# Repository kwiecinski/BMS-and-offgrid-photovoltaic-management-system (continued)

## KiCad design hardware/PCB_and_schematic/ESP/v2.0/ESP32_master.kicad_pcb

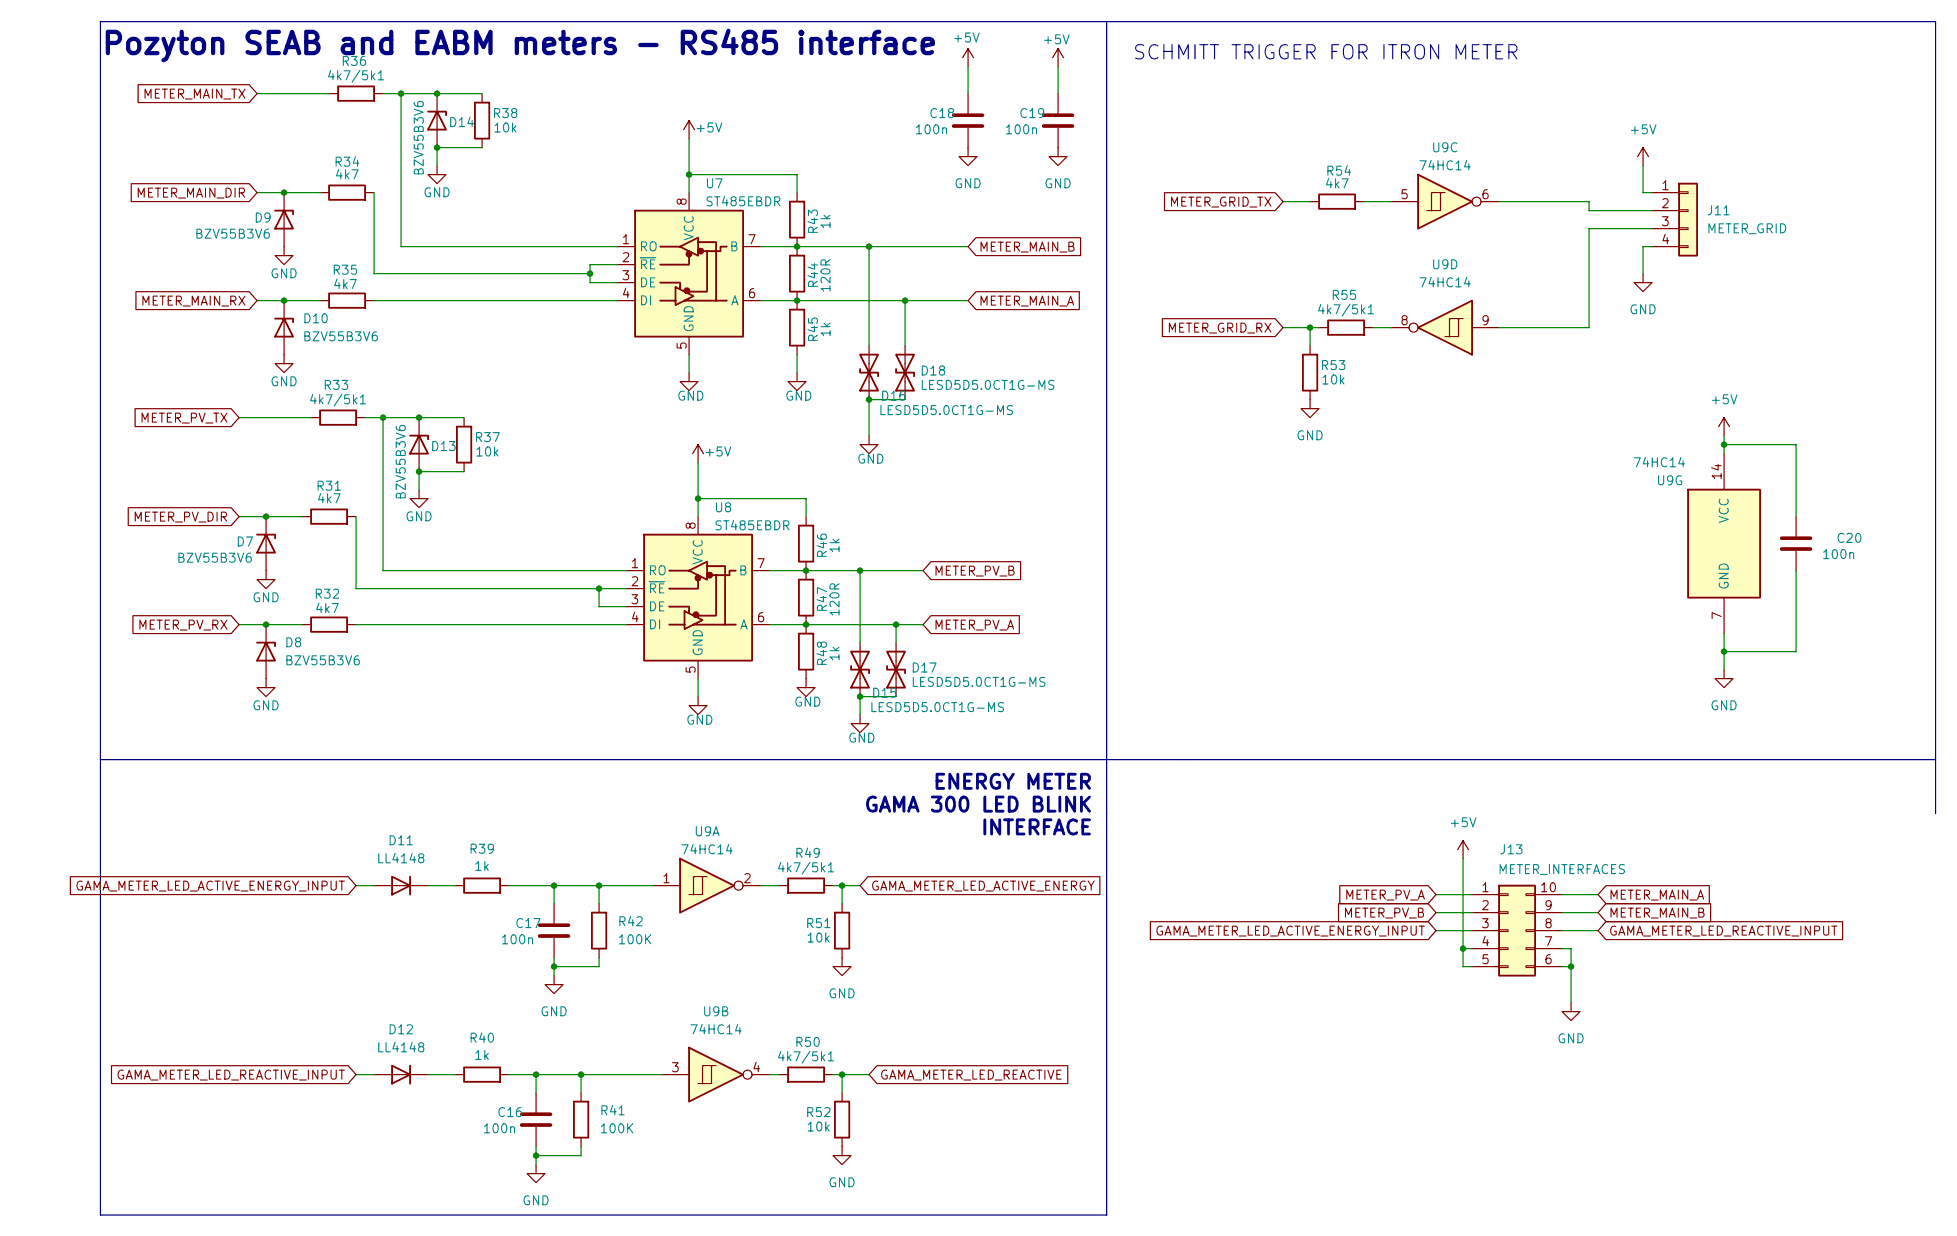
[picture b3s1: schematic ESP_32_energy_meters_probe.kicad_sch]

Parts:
C16, C17, C18, C19, C20: 100n; C_0805_2012Metric_Pad1.18x1.45mm_HandSolder
D7, D8, D9, D10, D13, D14: BZV55B3V6; D_MiniMELF
D11, D12: LL4148; D_MiniMELF
D15, D16, D17, D18: LESD5D5.0CT1G-MS; D_SOD-523
J11: METER_GRID; JST_XA_B04B-XASK-1_1x04_P2.50mm_Vertical
J13: METER_INTERFACES; CDDC-1,5-5-PV-3,5
R31, R32, R34, R35, R54: 4k7; R_0805_2012Metric_Pad1.20x1.40mm_HandSolder
R33, R36, R49, R50, R55: 4k7/5k1; R_0805_2012Metric_Pad1.20x1.40mm_HandSolder
R37, R38, R51, R52, R53: 10k; R_0805_2012Metric_Pad1.20x1.40mm_HandSolder
R39, R40, R43, R45, R46, R48: 1k; R_0805_2012Metric_Pad1.20x1.40mm_HandSolder
R41, R42: 100K; R_0805_2012Metric_Pad1.20x1.40mm_HandSolder
R44, R47: 120R; R_0805_2012Metric_Pad1.20x1.40mm_HandSolder
U7, U8: ST485EBDR; SOIC-8_3.9x4.9mm_P1.27mm
U9: 74HC14; SOIC-14_3.9x8.7mm_P1.27mm

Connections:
+5V: C18.1, C19.1, C20.1, J11.1, J13.4, J13.5, R43.2, R46.2, U7.8 (VCC), U8.8 (VCC), U9.14 (VCC); also elsewhere on the board
GAMA_METER_LED_ACTIVE_ENERGY: R49.1, R51.2; also elsewhere on the board
GAMA_METER_LED_ACTIVE_ENERGY_INPUT: D11.2 (A), J13.3
GAMA_METER_LED_REACTIVE: R50.1, R52.2; also elsewhere on the board
GAMA_METER_LED_REACTIVE_INPUT: D12.2 (A), J13.8
GND: C16.2, C17.2, C18.2, C19.2, C20.2, D7.2 (A), D8.2 (A), D9.2 (A), D10.2 (A), D13.2 (A), D14.2 (A), D15.1 (A1), D16.1 (A1), D17.1 (A1), D18.1 (A1), J11.4, J13.6, J13.7, R37.1, R38.1, R41.1, R42.1, R45.1, R48.1, R51.1, R52.1, R53.1, U7.5 (GND), U8.5 (GND), U9.7 (GND); also elsewhere on the board
METER_GRID_RX: R53.2, R55.1; also elsewhere on the board
METER_GRID_TX: R54.1; also elsewhere on the board
METER_MAIN_A: D18.2 (A2), J13.10, R44.1, R45.2, U7.6 (A)
METER_MAIN_B: D16.2 (A2), J13.9, R43.1, R44.2, U7.7 (B)
METER_MAIN_DIR: D9.1 (K), R34.1; also elsewhere on the board
METER_MAIN_RX: D10.1 (K), R35.1; also elsewhere on the board
METER_MAIN_TX: R36.1; also elsewhere on the board
METER_PV_A: D17.2 (A2), J13.1, R47.1, R48.2, U8.6 (A)
METER_PV_B: D15.2 (A2), J13.2, R46.1, R47.2, U8.7 (B)
METER_PV_DIR: D7.1 (K), R31.1; also elsewhere on the board
METER_PV_RX: D8.1 (K), R32.1; also elsewhere on the board
METER_PV_TX: R33.1; also elsewhere on the board
unnamed: C16.1, R40.2, R41.2, U9.3
unnamed: C17.1, R39.2, R42.2, U9.1
unnamed: D11.1 (K), R39.1
unnamed: D12.1 (K), R40.1
unnamed: D13.1 (K), R33.2, R37.2, U8.1 (RO)
unnamed: D14.1 (K), R36.2, R38.2, U7.1 (RO)
unnamed: J11.2, U9.6
unnamed: J11.3, U9.9
unnamed: R49.2, U9.2
unnamed: R50.2, U9.4
unnamed: R54.2, U9.5
unnamed: R55.2, U9.8
unnamed: R34.2, U7.2 (~RE), U7.3 (DE)
unnamed: R35.2, U7.4 (DI)
unnamed: R31.2, U8.2 (~RE), U8.3 (DE)
unnamed: R32.2, U8.4 (DI)

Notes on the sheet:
Pozyton SEAB and EABM meters - RS485 interface
ENERGY METER GAMA 300 LED BLINK INTERFACE
SCHMITT TRIGGER FOR ITRON METER

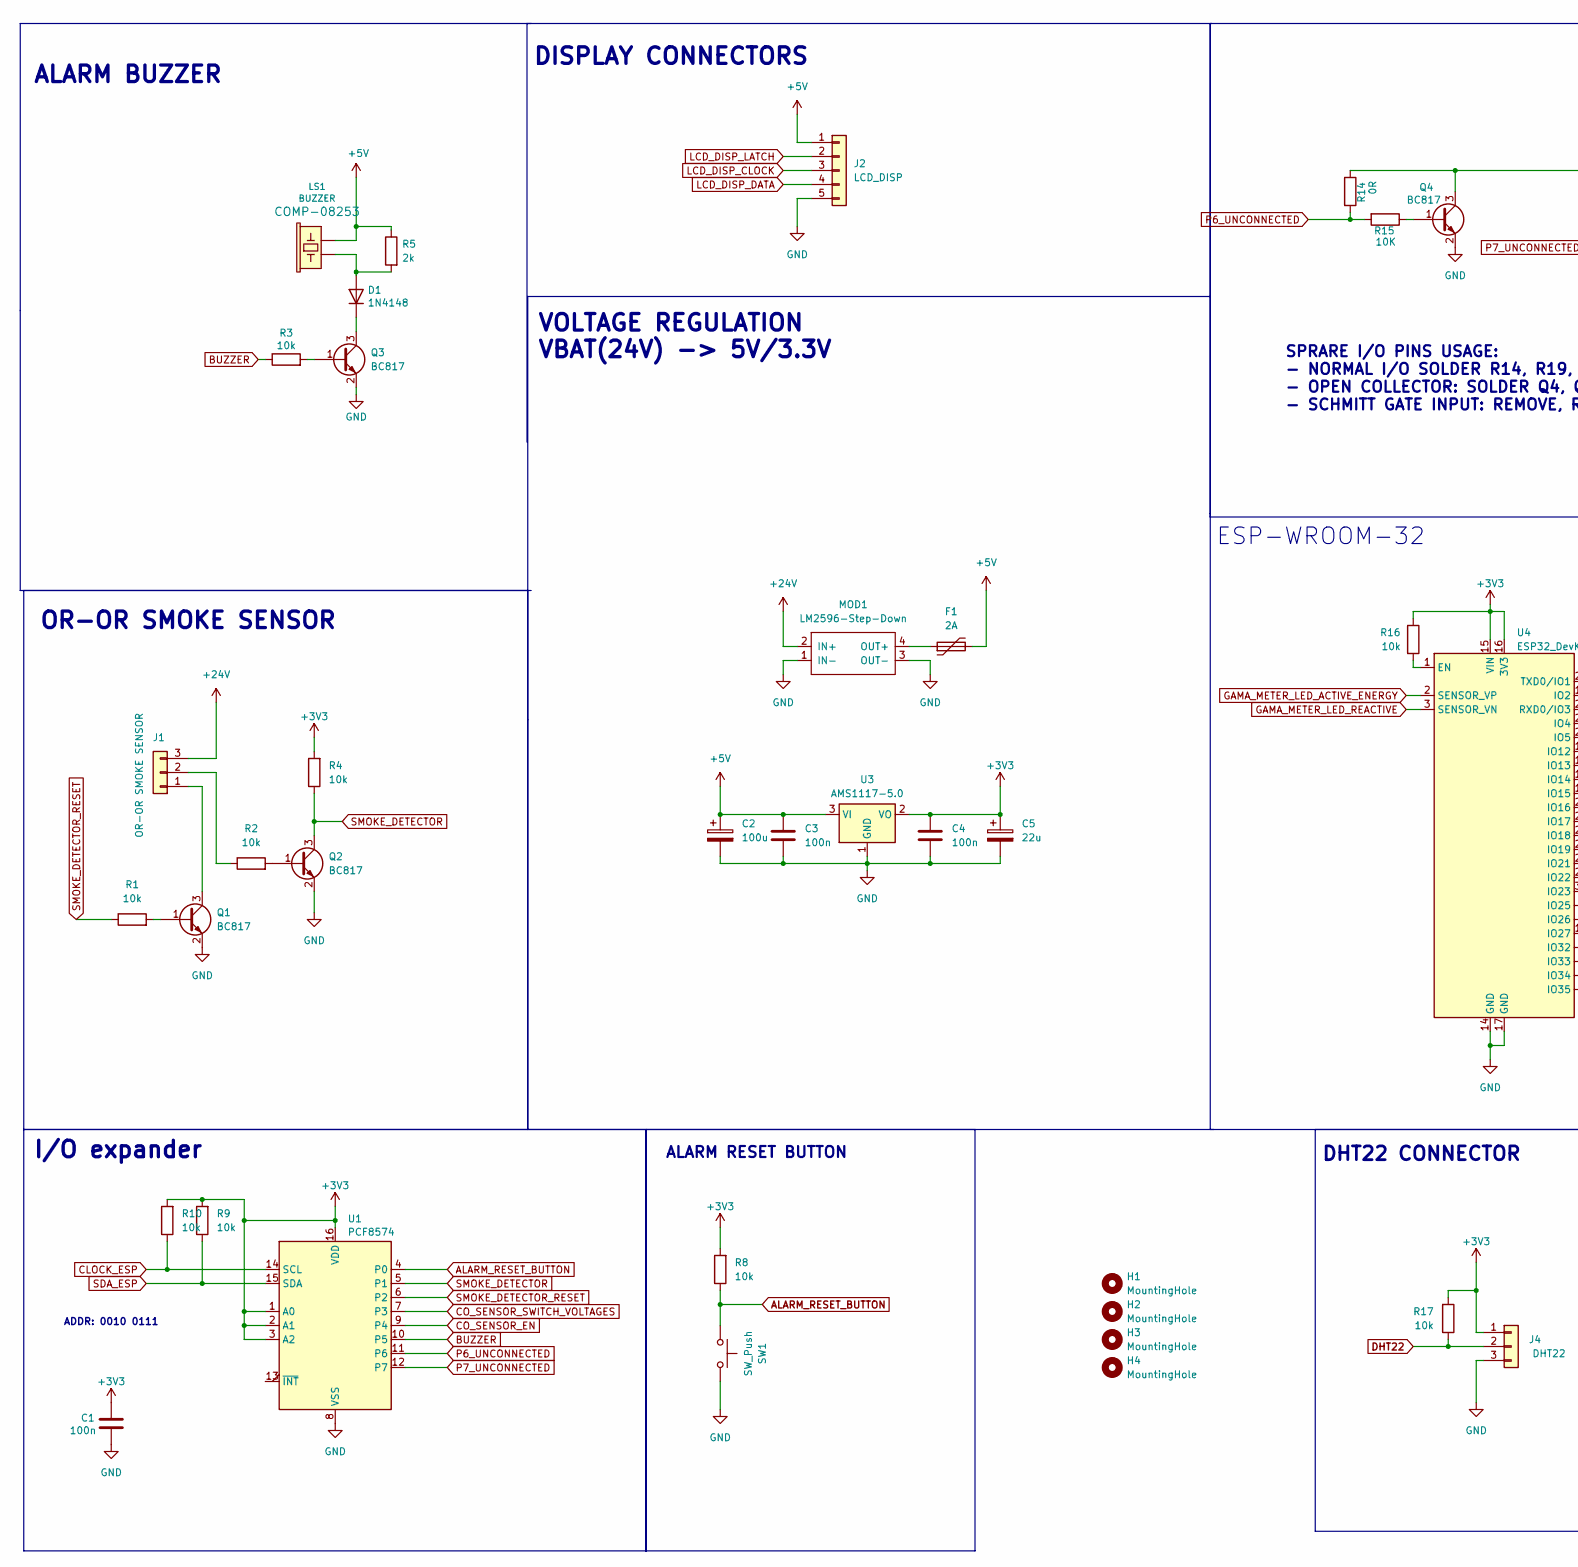
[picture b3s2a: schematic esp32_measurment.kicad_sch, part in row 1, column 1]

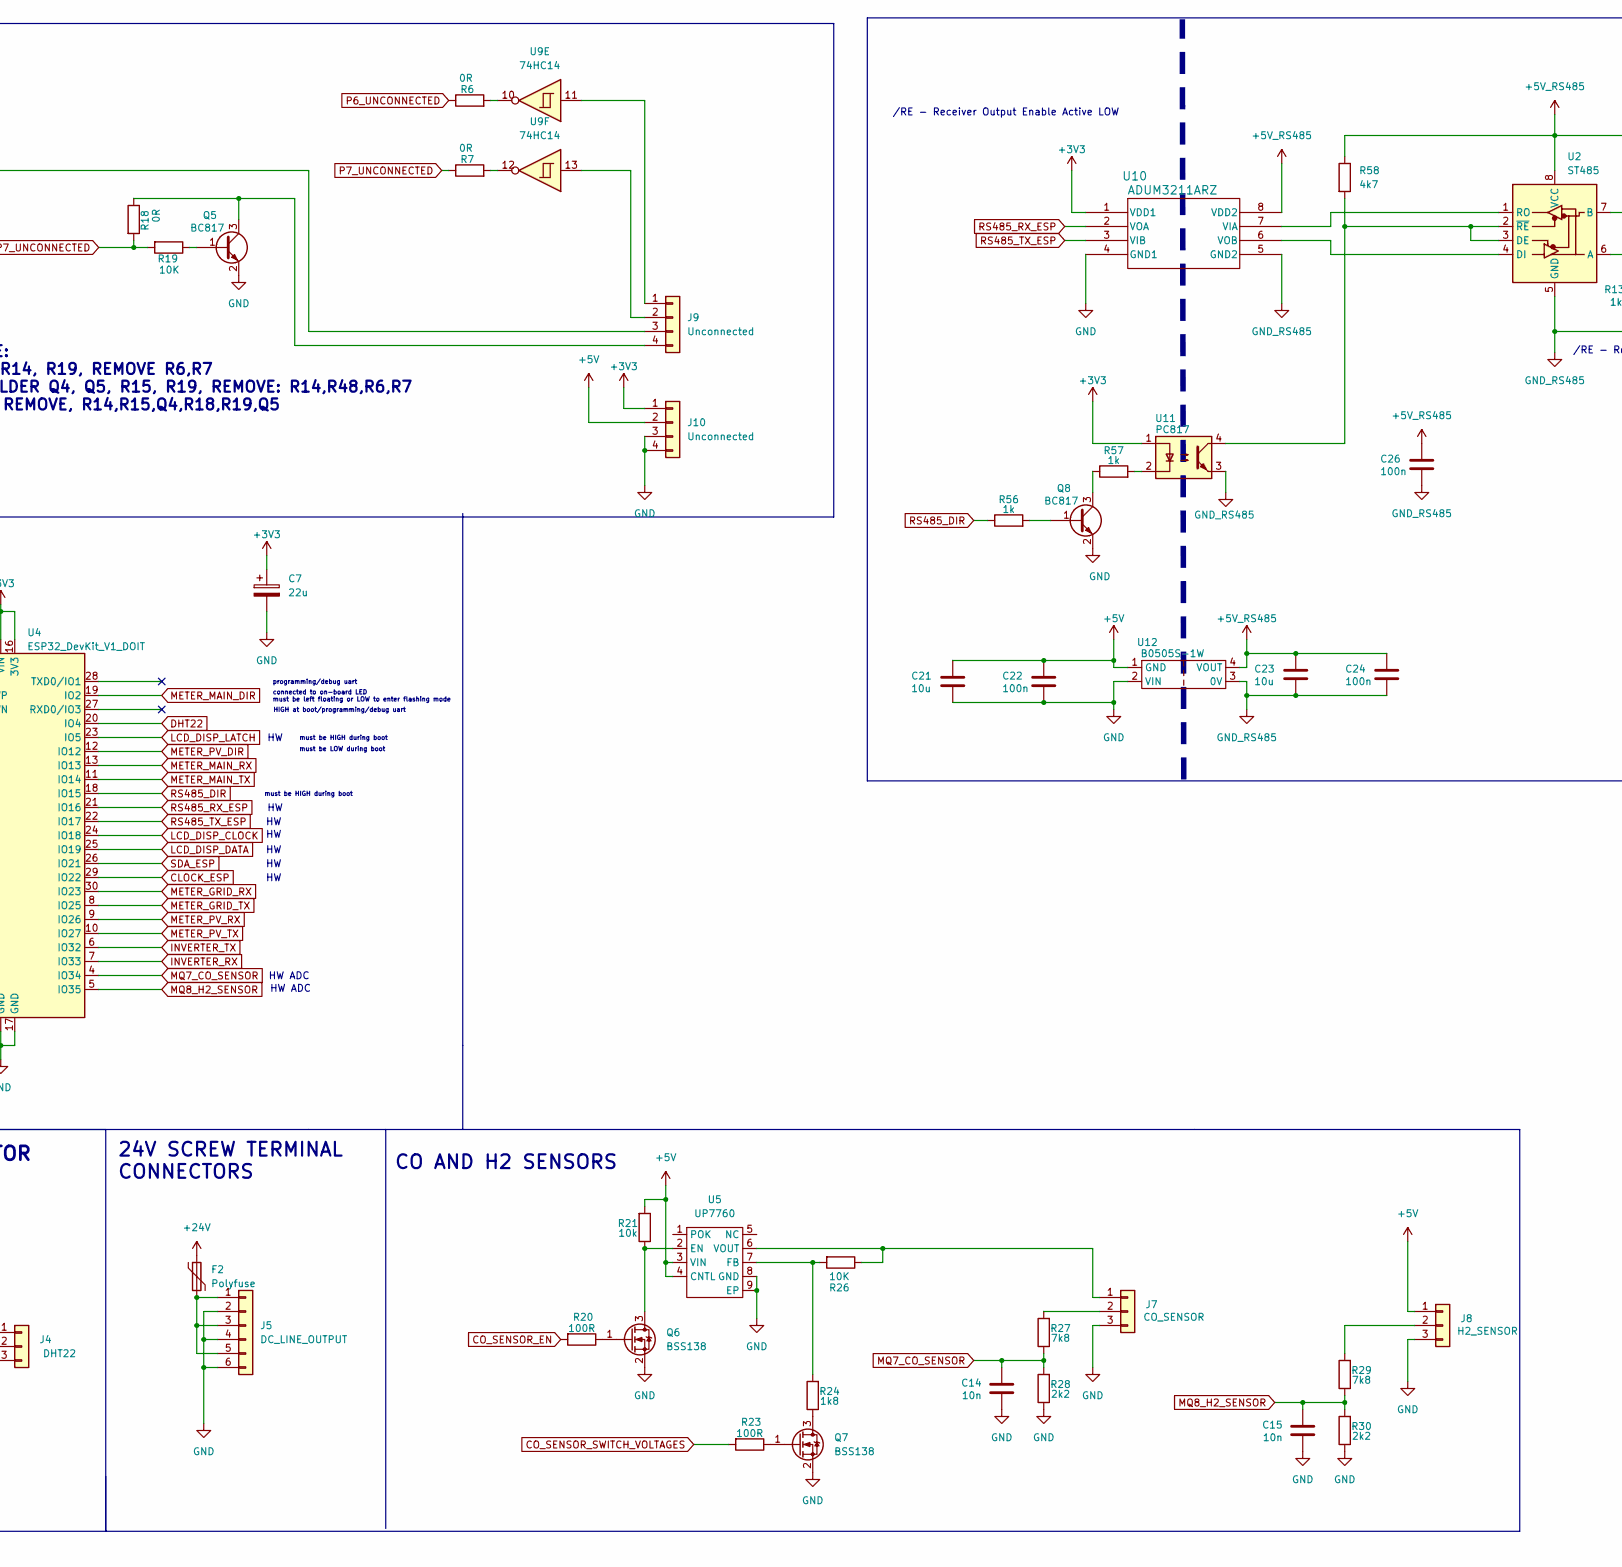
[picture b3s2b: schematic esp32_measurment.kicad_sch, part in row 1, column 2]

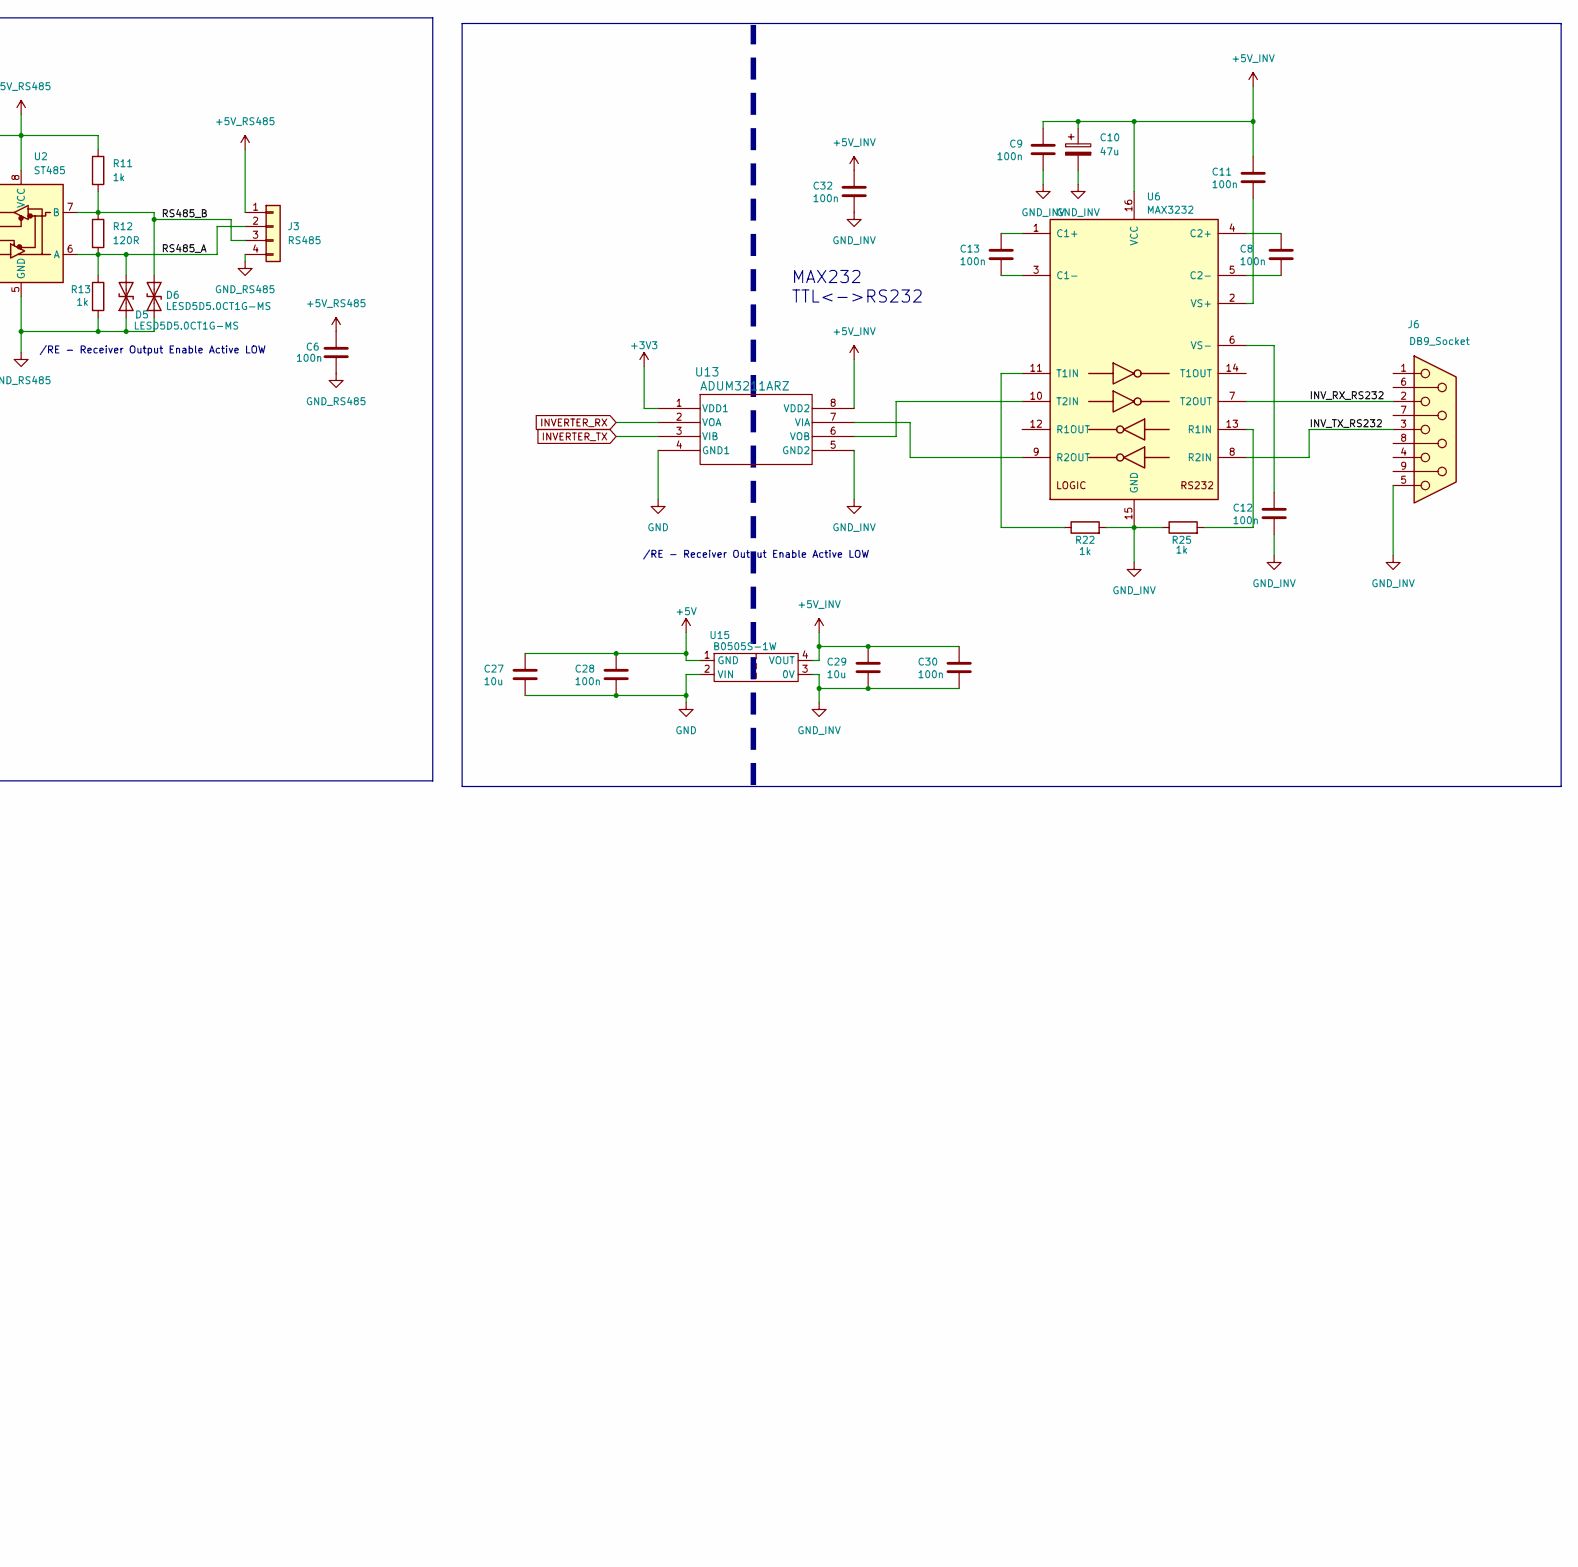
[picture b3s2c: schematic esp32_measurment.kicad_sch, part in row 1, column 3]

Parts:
C1, C3, C4, C6, C8, C11, C12, C13, C22, C24, C26, C28, C30, C32: 100n; C_0805_2012Metric_Pad1.18x1.45mm_HandSolder
C2: 100u; CP_Radial_D4.0mm_P1.50mm
C5: 22u; CP_Radial_D4.0mm_P1.50mm
C7: 22u; CP_Radial_D5.0mm_P2.00mm
C9: 100n; C_0805_2012Metric
C10: 47u; CP_Radial_D5.0mm_P2.00mm
C14, C15: 10n; C_0805_2012Metric
C21, C23, C27, C29: 10u; C_1206_3216Metric
D1: 1N4148; D_MiniMELF
D5, D6: LESD5D5.0CT1G-MS; D_SOD-523
F1: 2A; Fuse_2512_6332Metric_Pad1.52x3.35mm_HandSolder
F2: Polyfuse; Fuse_2920_7451Metric
H1, H2, H3, H4: MountingHole; Mount-Hole-3mm
J1: OR-OR SMOKE SENSOR; JST_XA_B03B-XASK-1_1x03_P2.50mm_Vertical
J2: LCD_DISP; JST_XA_B05B-XASK-1_1x05_P2.50mm_Vertical
J3: RS485; JST_XH_B4B-XH-A_1x04_P2.50mm_Vertical
J4: DHT22; JST_XA_1x03_P2.54mm_Vertical
J5: DC_LINE_OUTPUT; Screw-Terminal-P6-rast-5mm-6,7x30
J6: DB9_Socket; DSUB-9_Female_Horizontal_P2.77x2.84mm_EdgePinOffset7.70mm_H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
J7: CO_SENSOR; JST_XA_B03B-XASK-1_1x03_P2.50mm_Vertical
J8: H2_SENSOR; JST_XA_B03B-XASK-1_1x03_P2.50mm_Vertical
J9, J10: Unconnected; JST_XA_B04B-XASK-1_1x04_P2.50mm_Vertical
LS1: BUZZER; Buzzer
MOD1: LM2596-Step-Down; LM2596-Step-Down-Conv
Q1, Q2, Q3, Q4, Q5, Q8: BC817; SOT-23
Q6, Q7: BSS138; SOT-23
R1, R2, R3, R4, R8, R9, R10, R16, R17, R21: 10k; R_0805_2012Metric_Pad1.20x1.40mm_HandSolder
R5: 2k; C_0805_2012Metric
R6, R7, R14, R18: 0R; R_0805_2012Metric_Pad1.20x1.40mm_HandSolder
R11, R13, R22, R25, R56, R57: 1k; R_0805_2012Metric_Pad1.20x1.40mm_HandSolder
R12: 120R; R_0805_2012Metric_Pad1.20x1.40mm_HandSolder
R15, R19, R26: 10K; R_0805_2012Metric_Pad1.20x1.40mm_HandSolder
R20, R23: 100R; R_0805_2012Metric_Pad1.20x1.40mm_HandSolder
R24: 1k8; R_0805_2012Metric_Pad1.20x1.40mm_HandSolder
R27, R29: 7k8; R_0805_2012Metric_Pad1.20x1.40mm_HandSolder
R28, R30: 2k2; R_0805_2012Metric_Pad1.20x1.40mm_HandSolder
R58: 4k7; R_0805_2012Metric_Pad1.20x1.40mm_HandSolder
SW1: SW_Push; JST_XA_B02B-XASK-1_1x02_P2.50mm_Vertical
U1: PCF8574; DIP-16_W7.62mm_LongPads
U2: ST485; SOIC-8_3.9x4.9mm_P1.27mm
U3: AMS1117-5.0; SOT-223-3_TabPin2
U4: ESP32_DevKit_V1_DOIT; esp32_devkit_v1_doit
U5: UP7760; SOIC-8-1EP_3.9x4.9mm_P1.27mm_EP2.41x3.81mm
U6: MAX3232; SO-16_3.9x9.9mm_P1.27mm
U9: 74HC14; SOIC-14_3.9x8.7mm_P1.27mm
U10, U13: ADUM3211ARZ; SO-8_3.9x4.9mm_P1.27mm
U11: PC817; DIP-4_W7.62mm
U12, U15: B0505S-1W; B0505S

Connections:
+3V3: C1.1, C4.1, C5.1, C7.1, J4.1, J10.1, R4.2, R8.2, R9.2, R10.2, R16.1, R17.2, U1.1 (A0), U1.2 (A1), U1.3 (A2), U1.16 (VDD), U3.2 (VO), U4.15 (VIN), U4.16 (3V3), U10.1 (VDD1), U11.1, U13.1 (VDD1)
+5V: C2.1, C3.1, C21.1, C22.1, C27.1, C28.1, F1.2, J2.1, J8.1, J10.2, LS1.- (2), R5.1, R21.2, U3.3 (VI), U5.3 (VIN), U5.4 (CNTL), U12.1 (GND), U15.1 (GND); also elsewhere on the board
+5V_INV: C9.2, C10.1, C11.1, C29.1, C30.1, C32.1, U6.16 (VCC), U13.8 (VDD2), U15.4 (VOUT)
+5V_RS485: C6.1, C23.1, C24.1, C26.1, J3.1, R11.1, R58.1, U2.8 (VCC), U10.8 (VDD2), U12.4 (VOUT)
+24V: F2.1, J1.3, MOD1.2 (IN+)
/ESP32_Measurment_Board/INV_RX_RS232: J6.2, U6.7 (T2OUT)
/ESP32_Measurment_Board/INV_TX_RS232: J6.3, U6.8 (R2IN)
/ESP32_Measurment_Board/RS485_A: D5.2 (A2), J3.2, R12.2, R13.1, U2.6 (A)
/ESP32_Measurment_Board/RS485_B: D6.2 (A2), J3.3, R11.2, R12.1, U2.7 (B)
ALARM_RESET_BUTTON: R8.1, SW1.1, U1.4 (P0)
BUZZER: R3.1, U1.10 (P5)
CLOCK_ESP: R10.1, U1.14 (SCL), U4.29 (IO22)
CO_SENSOR_EN: R20.2, U1.9 (P4)
CO_SENSOR_SWITCH_VOLTAGES: R23.2, U1.7 (P3)
DHT22: J4.2, R17.1, U4.20 (IO4)
GAMA_METER_LED_ACTIVE_ENERGY: U4.2 (SENSOR_VP); also elsewhere on the board
GAMA_METER_LED_REACTIVE: U4.3 (SENSOR_VN); also elsewhere on the board
GND: C1.2, C2.2, C3.2, C4.2, C5.2, C7.2, C14.1, C15.1, C21.2, C22.2, C27.2, C28.2, J2.5, J4.3, J5.2, J5.4, J5.6, J7.3, J8.3, J10.3, J10.4, MOD1.1 (IN-), MOD1.3 (OUT-), Q1.2 (E), Q2.2 (E), Q3.2 (E), Q4.2 (E), Q5.2 (E), Q6.2 (S), Q7.2 (S), Q8.2 (E), R28.1, R30.1, SW1.2, U1.8 (VSS), U3.1 (GND), U4.14 (GND), U4.17 (GND), U5.8 (GND), U5.9 (EP), U10.4 (GND1), U12.2 (VIN), U13.4 (GND1), U15.2 (VIN); also elsewhere on the board
GND_INV: C9.1, C10.2, C12.2, C29.2, C30.2, C32.2, J6.5, R22.2, R25.1, U6.15 (GND), U13.5 (GND2), U15.3 (0V)
GND_RS485: C6.2, C23.2, C24.2, C26.2, D5.1 (A1), D6.1 (A1), J3.4, R13.2, U2.5 (GND), U10.5 (GND2), U11.3, U12.3 (0V)
INVERTER_RX: U4.7 (IO33), U13.2 (VOA)
INVERTER_TX: U4.6 (IO32), U13.3 (VIB)
LCD_DISP_CLOCK: J2.3, U4.24 (IO18)
LCD_DISP_DATA: J2.4, U4.25 (IO19)
LCD_DISP_LATCH: J2.2, U4.23 (IO5)
METER_GRID_RX: U4.30 (IO23); also elsewhere on the board
METER_GRID_TX: U4.8 (IO25); also elsewhere on the board
METER_MAIN_DIR: U4.19 (IO2); also elsewhere on the board
METER_MAIN_RX: U4.13 (IO13); also elsewhere on the board
METER_MAIN_TX: U4.11 (IO14); also elsewhere on the board
METER_PV_DIR: U4.12 (IO12); also elsewhere on the board
METER_PV_RX: U4.9 (IO26); also elsewhere on the board
METER_PV_TX: U4.10 (IO27); also elsewhere on the board
MQ7_CO_SENSOR: C14.2, R27.1, R28.2, U4.4 (IO34)
MQ8_H2_SENSOR: C15.2, R29.1, R30.2, U4.5 (IO35)
unnamed: D1.2 (A), LS1.+ (1), R5.2
unnamed: D1.1 (K), Q3.3 (C)
unnamed: J1.1, Q1.3 (C)
unnamed: J1.2, R2.1
unnamed: F2.2, J5.1, J5.3, J5.5
unnamed: J7.1, R26.1, U5.6 (VOUT)
unnamed: J7.2, R27.2
unnamed: J8.2, R29.2
unnamed: J9.1, U9.11
unnamed: J9.2, U9.13
unnamed: J9.3, Q4.3 (C), R14.1
unnamed: J9.4, Q5.3 (C), R18.1
unnamed: F1.1, MOD1.4 (OUT+)
unnamed: Q1.1 (B), R1.2
unnamed: Q2.1 (B), R2.2
unnamed: Q3.1 (B), R3.2
unnamed: Q4.1 (B), R15.1
unnamed: Q5.1 (B), R19.1
unnamed: Q6.3 (D), R21.1, U5.2 (EN)
unnamed: Q6.1 (G), R20.1
unnamed: Q7.3 (D), R24.1
unnamed: Q7.1 (G), R23.1
unnamed: Q8.1 (B), R56.2
unnamed: Q8.3 (C), R57.1
unnamed: R6.2, U9.10
unnamed: R7.2, U9.12
unnamed: R57.2, U11.2
unnamed: R58.2, U2.2 (~RE), U2.3 (DE), U11.4
unnamed: R16.2, U4.1 (EN)
unnamed: R24.2, R26.2, U5.7 (FB)
unnamed: C13.1, U6.1 (C1+)
unnamed: C13.2, U6.3 (C1-)
unnamed: C8.1, U6.4 (C2+)
unnamed: C8.2, U6.5 (C2-)
unnamed: R25.2, U6.13 (R1IN)
unnamed: R22.1, U6.11 (T1IN)
unnamed: C11.2, U6.2 (VS+)
unnamed: C12.1, U6.6 (VS-)
unnamed: U2.1 (RO), U10.7 (VIA)
unnamed: U2.4 (DI), U10.6 (VOB)
unnamed: U6.9 (R2OUT), U13.7 (VIA)
unnamed: U6.10 (T2IN), U13.6 (VOB)
P6_UNCONNECTED: R6.1, R14.2, R15.2, U1.11 (P6)
P7_UNCONNECTED: R7.1, R18.2, R19.2, U1.12 (P7)
RS485_DIR: R56.1, U4.18 (IO15)
RS485_RX_ESP: U4.21 (IO16), U10.2 (VOA)
RS485_TX_ESP: U4.22 (IO17), U10.3 (VIB)
SDA_ESP: R9.1, U1.15 (SDA), U4.26 (IO21)
SMOKE_DETECTOR: Q2.3 (C), R4.1, U1.5 (P1)
SMOKE_DETECTOR_RESET: R1.1, U1.6 (P2)

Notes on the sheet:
programming/debug uart
ADDR: 0010 0111
DHT22 CONNECTOR
OR-OR SMOKE SENSOR
ESP-WROOM-32
I/O expander
must be HIGH during boot
/RE - Receiver Output Enable Active LOW
HIGH at boot/programming/debug uart
HW ADC
MAX232 TTL<->RS232
must be LOW during boot
DISPLAY CONNECTORS
connected to on-board LED must be left floating or LOW to enter flashing mode
SPRARE I/O PINS USAGE: - NORMAL I/O SOLDER R14, R19, REMOVE R6,R7 - OPEN COLLECTOR: SOLDER Q4, Q5, R15, R19, REMOVE: R14,R48,R6,R7 - SCHMITT GATE INPUT: REMOVE, R14,R15,Q4,R18,R19,Q5
ALARM RESET BUTTON
CO AND H2 SENSORS
ALARM BUZZER
24V SCREW TERMINAL CONNECTORS
VOLTAGE REGULATION VBAT(24V) -> 5V/3.3V

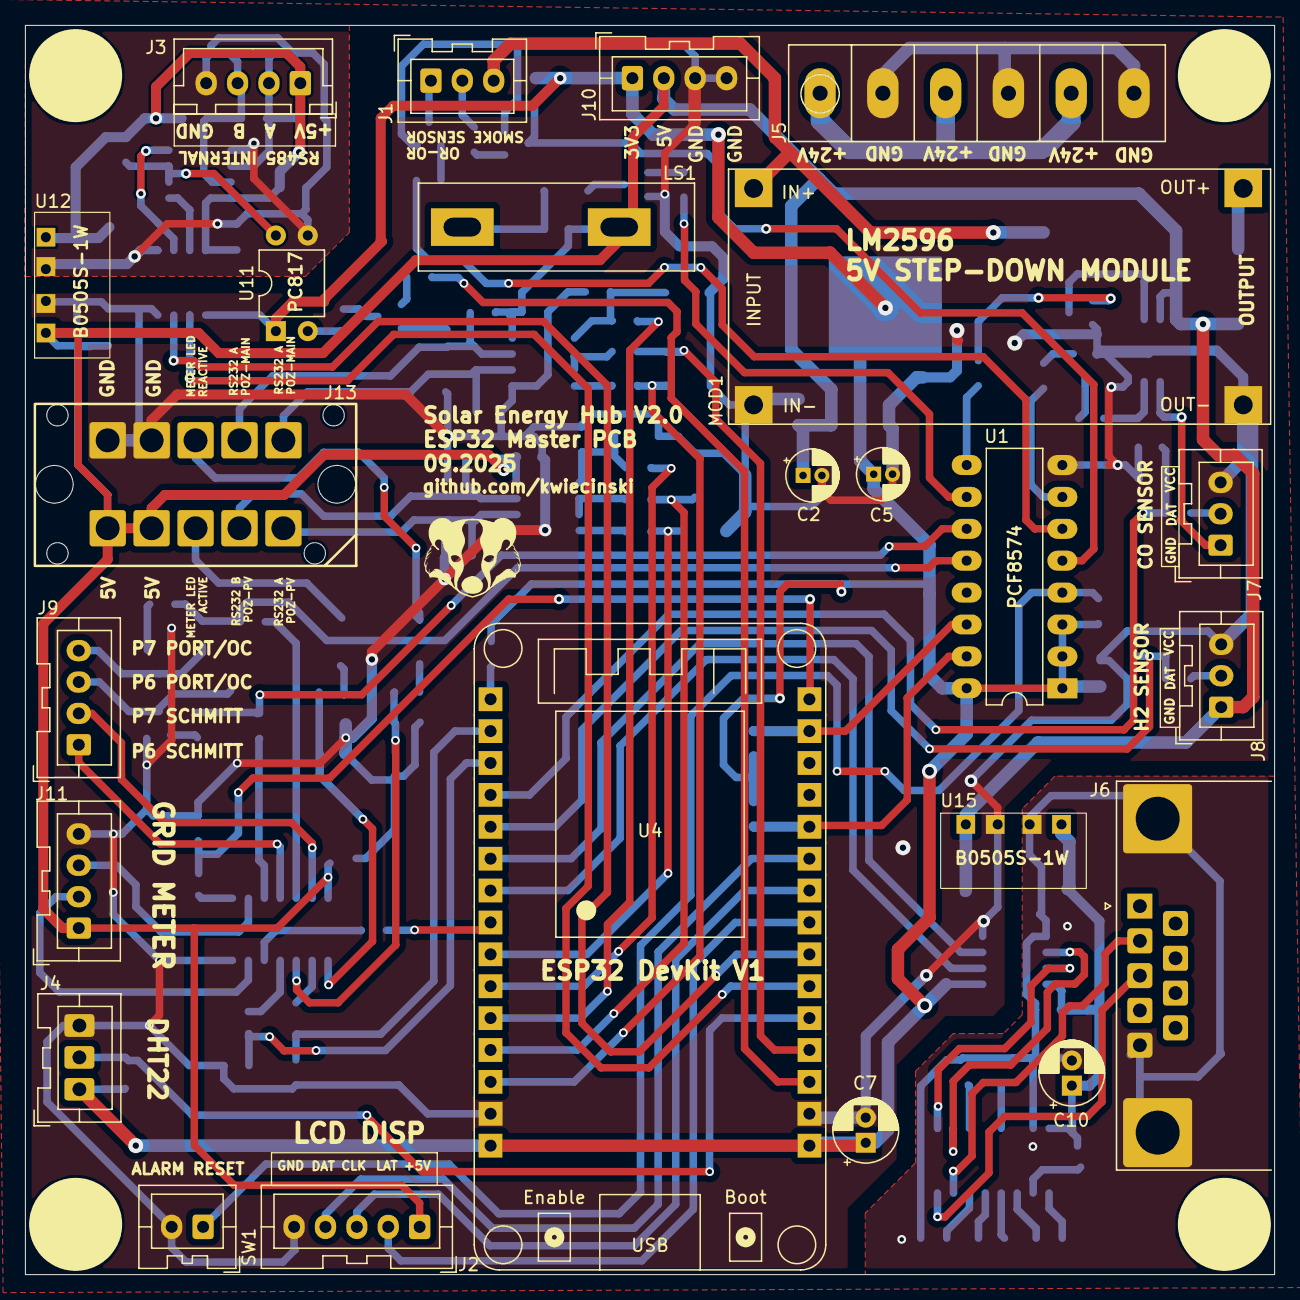
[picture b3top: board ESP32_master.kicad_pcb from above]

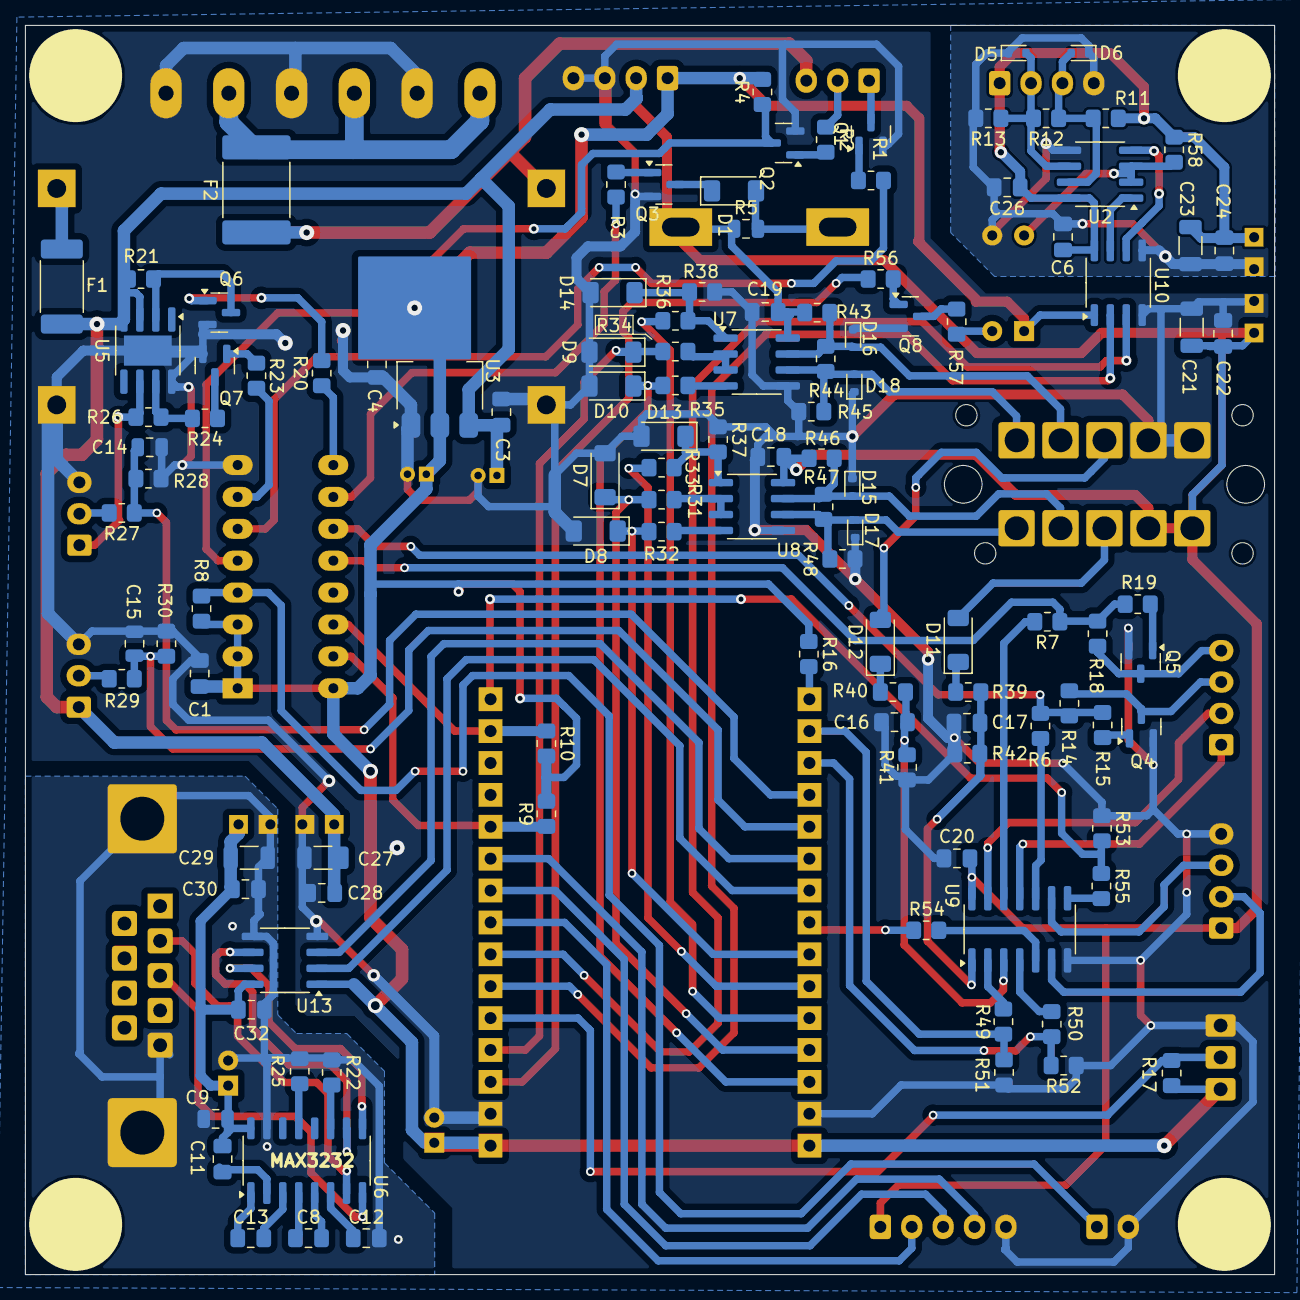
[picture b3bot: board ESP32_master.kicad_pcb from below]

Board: 2 copper layers, 99.5 x 99.5 mm, 146 parts (118 on the bottom side), 107 nets.
